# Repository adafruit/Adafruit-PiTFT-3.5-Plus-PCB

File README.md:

## Adafruit PiTFT 3.5 Plus Display PCB
<a href="http://www.adafruit.com/products/2441"><br/>
Click here to purchase one from the Adafruit shop</a>

This display for the Raspberry Pi features a 3.5" display with 480x320 16-bit color pixels and a resistive touch overlay just like our popular original, but this one is engineered specifically to work with the newer "2x20 connector" Raspberry Pi's. The plate uses the high speed SPI interface on the Pi and can use the mini display as a console, X window port, displaying images or video etc. Best of all it plugs right in on top!

This PiTFT 3.5" is designed to fit nicely onto the Raspberry Pi Zero, Pi 3, Pi 2 or Model A+ / B+ (any Pi with a 2x20 connector). Not for use with an old Pi 1 with 2x13 connector If you'd like to use a 3.5" display with the original Pi A or Pi B, check out this version

PCB files for the Adafruit PiTFT 3.5" Plus. The format is EagleCAD schematic and board layout
- https://www.adafruit.com/product/2441

### License

Adafruit invests time and resources providing this open source design, please support Adafruit and open-source hardware by purchasing products from [Adafruit](https://www.adafruit.com)!

All text above must be included in any redistribution

Designed by Limor Fried/Ladyada for Adafruit Industries.
Creative Commons Attribution/Share-Alike, all text above must be included in any redistribution. 
See license.txt for additional information.

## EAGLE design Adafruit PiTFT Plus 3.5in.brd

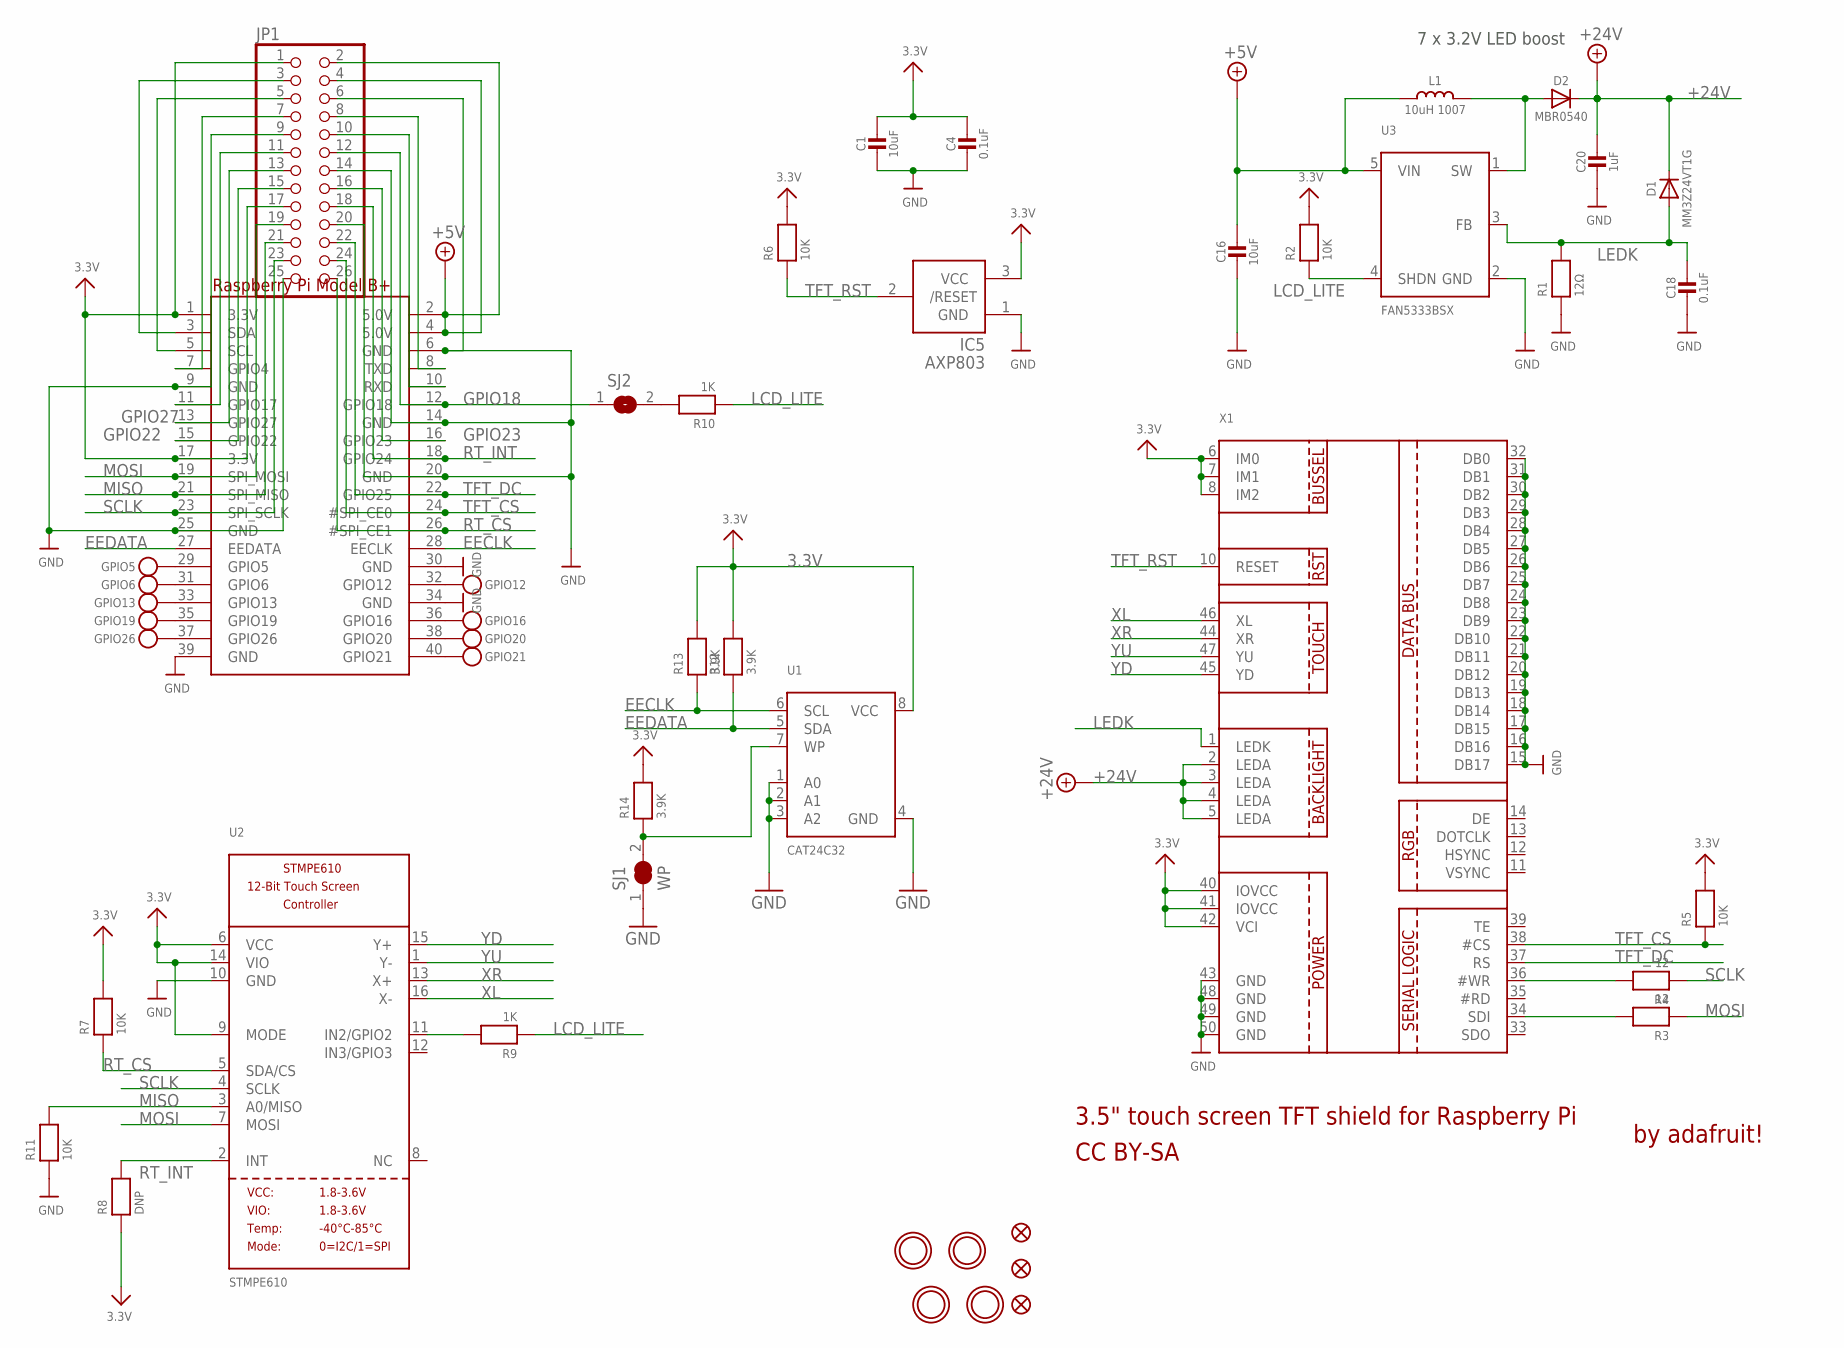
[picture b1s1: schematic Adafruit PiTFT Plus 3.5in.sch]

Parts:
C1, C16: 10uF; 0805-NO
C4, C18: 0.1uF; 0805-NO
C20: 1uF; _0805MP
D1: MM3Z24VT1G; SMADIODE
D2: MBR0540; SOD-123
GPIO5, GPIO6, GPIO12, GPIO13, GPIO16, GPIO19, GPIO20, GPIO21, GPIO26: TESTPOINT1.5X2.0MM_NOCREAM; PAD-1.5X2.0
IC5: AXP803; SOT23
JP1: HEADER-2X13-SMT; 2X13_SMT_MALE
L1: 10uH 1007; INDUCTOR_1007
R1: 12Ω; 0805-NO
R2, R5, R6, R7, R11: 10K; 0805-NO
R3: 12; _0805MP
R4: 12; 0805-NO
R8: DNP; 0805-NO
R9: 1K; _0805MP
R10: 1K; 0805-NO
R12, R13, R14: 3.9K; 0805-NO
RPI1: RASPBERRYPI_BPLUS_SMT; RASPBERRYPI_BPLUS_SHIELD_SMT
SJ1: WP; SOLDERJUMPER_CLOSEDWIRE
SJ2: SOLDERJUMPERCLOSED; SOLDERJUMPER_CLOSEDWIRE
U1: CAT24C32; SOIC8_150MIL
U2: STMPE610; QFN16_3MM
U3: FAN5333BSX; SOT23-5@1
U$10, U$11, U$18: FIDUCIAL""; FIDUCIAL_1MM
U$15, U$16, U$17, U$20: MOUNTINGHOLE2.5_THICK; MOUNTINGHOLE_2.5_PLATED_THICK
X1: DISP_LCD_3.5IN_320X480_50PIN; TFT_3.5IN_320X480_50PIN

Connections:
3.3V: C1.1, C4.1, IC5.3 (VCC), JP1.1, JP1.17, R2.2, R5.2, R6.2, R7.2, R8.1, R12.2, R13.2, R14.2, RPI1.1 (3.3V), RPI1.17 (3.3V), U1.8 (VCC), U2.6 (VCC), U2.9 (MODE), U2.14 (VIO), X1.6 (IM0), X1.7 (IM1), X1.8 (IM2), X1.40 (IOVCC), X1.41 (IOVCC), X1.42 (VCI)
+5V: C16.1, JP1.2, JP1.4, L1.P$1 (1), RPI1.2 (5.0V), RPI1.4 (5.0V), U3.5 (VIN)
+24V: C20.1, D1.C, D2.C, X1.2 (LEDA), X1.3 (LEDA), X1.4 (LEDA), X1.5 (LEDA)
EECLK: R13.1, RPI1.28 (EECLK), U1.6 (SCL)
EEDATA: R12.1, RPI1.27 (EEDATA), U1.5 (SDA)
GND: C1.2, C4.2, C16.2, C18.2, C20.2, IC5.1 (GND), JP1.6, JP1.9, JP1.14, JP1.20, JP1.25, R1.1, R11.1, RPI1.6 (GND), RPI1.9 (GND), RPI1.14 (GND), RPI1.20 (GND), RPI1.25 (GND), RPI1.30 (GND), RPI1.34 (GND), RPI1.39 (GND), SJ1.1, U1.1 (A0), U1.2 (A1), U1.3 (A2), U1.4 (GND), U2.10 (GND), U3.2 (GND), X1.15 (DB17), X1.16 (DB16), X1.17 (DB15), X1.18 (DB14), X1.19 (DB13), X1.20 (DB12), X1.21 (DB11), X1.22 (DB10), X1.23 (DB9), X1.24 (DB8), X1.25 (DB7), X1.26 (DB6), X1.27 (DB5), X1.28 (DB4), X1.29 (DB3), X1.30 (DB2), X1.31 (DB1), X1.32 (DB0), X1.43 (GND), X1.48 (GND), X1.49 (GND), X1.50 (GND)
GPIO6: GPIO6.P$1, RPI1.31 (GPIO6)
GPIO16: GPIO16.P$1, RPI1.36 (GPIO16)
GPIO18: JP1.12, RPI1.12 (GPIO18), SJ2.1
GPIO22: JP1.15, RPI1.15 (GPIO22)
GPIO23: JP1.16, RPI1.16 (GPIO23)
GPIO27: JP1.13, RPI1.13 (GPIO27)
LCD_LITE: R2.1, R9.1, R10.1, U3.4 (SHDN)
LEDK: C18.1, D1.A, R1.2, U3.3 (FB), X1.1 (LEDK)
MISO: JP1.21, R11.2, RPI1.21 (SPI_MISO), U2.3 (A0/MISO)
MOSI: JP1.19, R3.1, RPI1.19 (SPI_MOSI), U2.7 (MOSI)
unnamed: R4.2, X1.36 (#WR)
unnamed: R3.2, X1.34 (SDI)
unnamed: R9.2, U2.11 (IN2/GPIO2)
unnamed: R10.2, SJ2.2
unnamed: GPIO5.P$1, RPI1.29 (GPIO5)
unnamed: JP1.3, RPI1.3 (SDA)
unnamed: JP1.5, RPI1.5 (SCL)
unnamed: JP1.7, RPI1.7 (GPIO4)
unnamed: GPIO13.P$1, RPI1.33 (GPIO13)
unnamed: GPIO19.P$1, RPI1.35 (GPIO19)
unnamed: JP1.11, RPI1.11 (GPIO17)
unnamed: D2.A, L1.P$2 (2), U3.1 (SW)
unnamed: GPIO26.P$1, RPI1.37 (GPIO26)
unnamed: GPIO12.P$1, RPI1.32 (GPIO12)
unnamed: GPIO20.P$1, RPI1.38 (GPIO20)
unnamed: R14.1, SJ1.2, U1.7 (WP)
unnamed: JP1.10, RPI1.10 (RXD)
unnamed: JP1.8, RPI1.8 (TXD)
unnamed: GPIO21.P$1, RPI1.40 (GPIO21)
RT_CS: JP1.26, R7.1, RPI1.26 (#SPI_CE1), U2.5 (SDA/CS)
RT_INT: JP1.18, R8.2, RPI1.18 (GPIO24), U2.2 (INT)
SCLK: JP1.23, R4.1, RPI1.23 (SPI_SCLK), U2.4 (SCLK)
TFT_CS: JP1.24, R5.1, RPI1.24 (#SPI_CE0), X1.38 (#CS)
TFT_DC: JP1.22, RPI1.22 (GPIO25), X1.37 (RS)
TFT_RST: IC5.2 (/RESET), R6.1, X1.10 (RESET)
XL: U2.16 (X-), X1.46 (XL)
XR: U2.13 (X+), X1.44 (XR)
YD: U2.15 (Y+), X1.45 (YD)
YU: U2.1 (Y-), X1.47 (YU)

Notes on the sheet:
3.5" touch screen TFT shield for Raspberry Pi
by adafruit!
CC BY-SA
7 x 3.2V LED boost

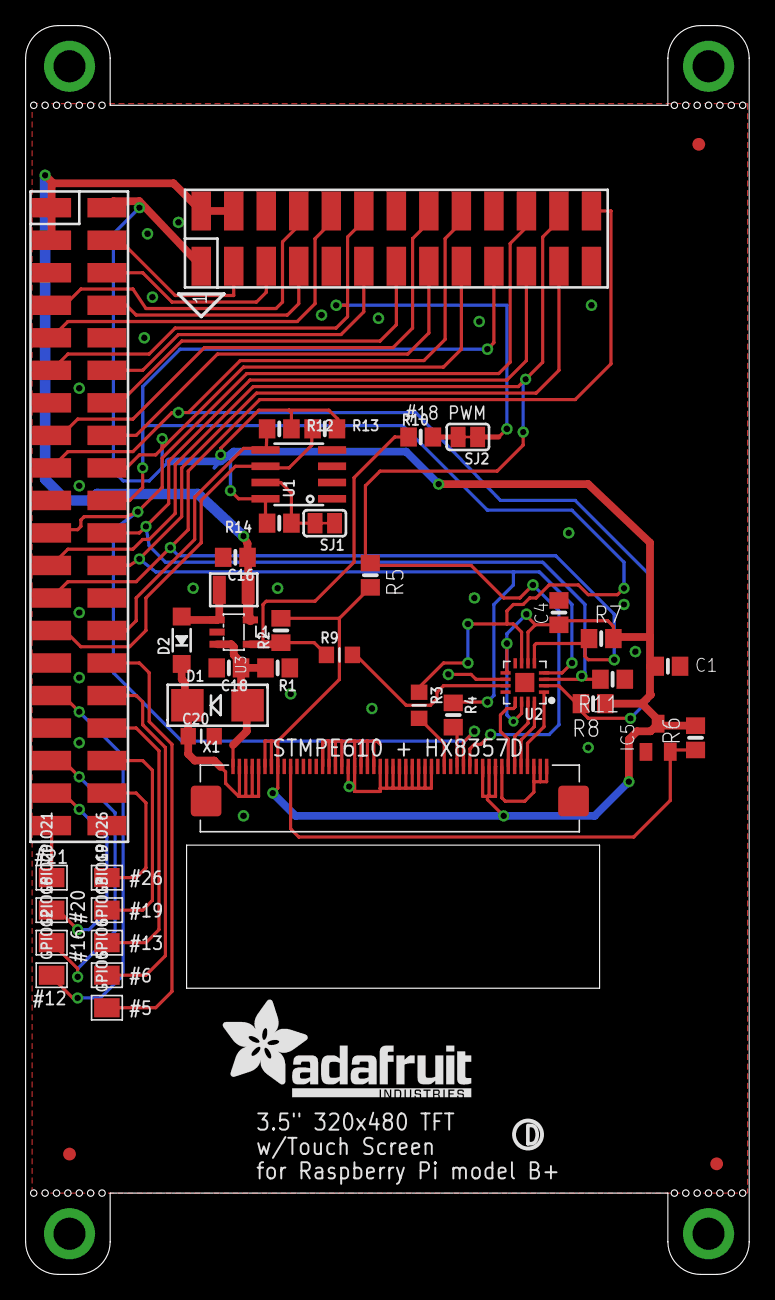
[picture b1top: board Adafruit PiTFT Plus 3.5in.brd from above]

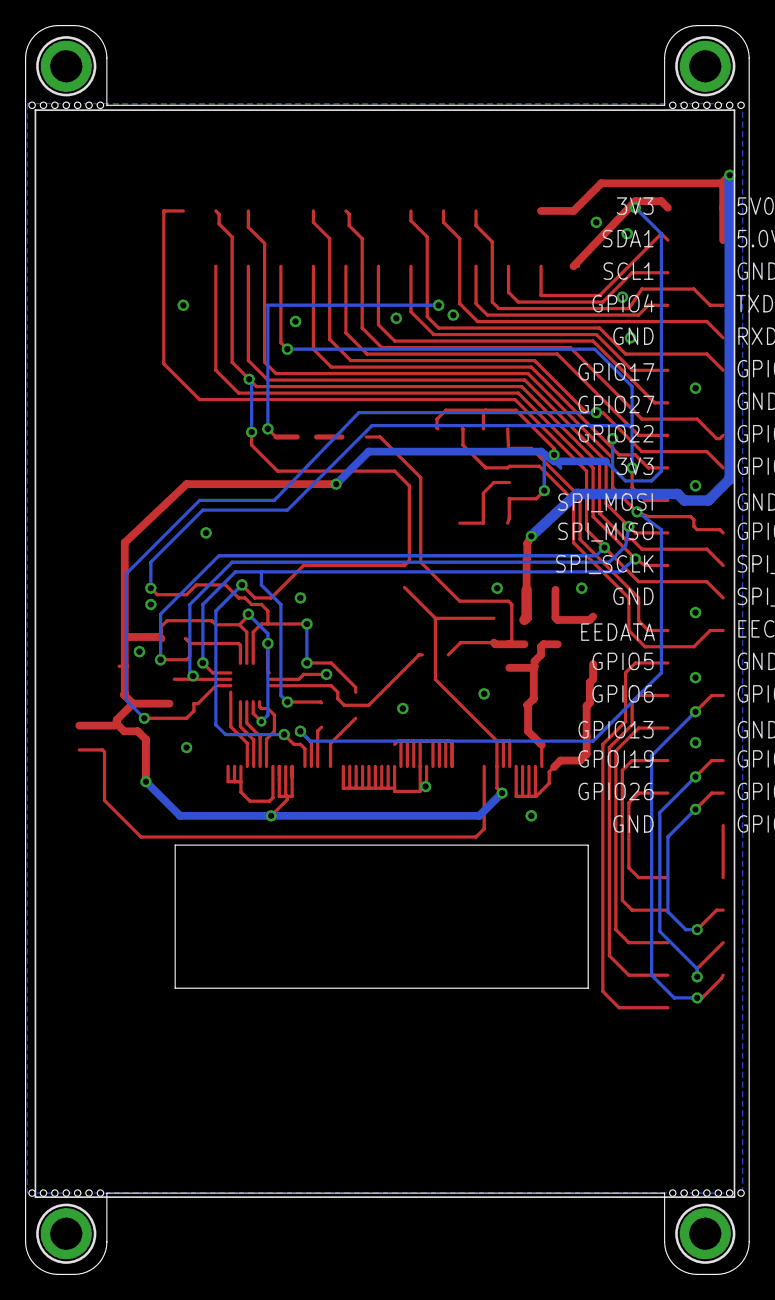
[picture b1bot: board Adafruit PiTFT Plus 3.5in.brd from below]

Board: 2 copper layers, 56.5 x 97.5 mm, 49 parts (6 on the bottom side), 45 nets.

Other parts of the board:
U$19: PCBFEAT-REV-056
U$23: ADAFRUIT_TEXT_20MM

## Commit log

2016-05-19 init
